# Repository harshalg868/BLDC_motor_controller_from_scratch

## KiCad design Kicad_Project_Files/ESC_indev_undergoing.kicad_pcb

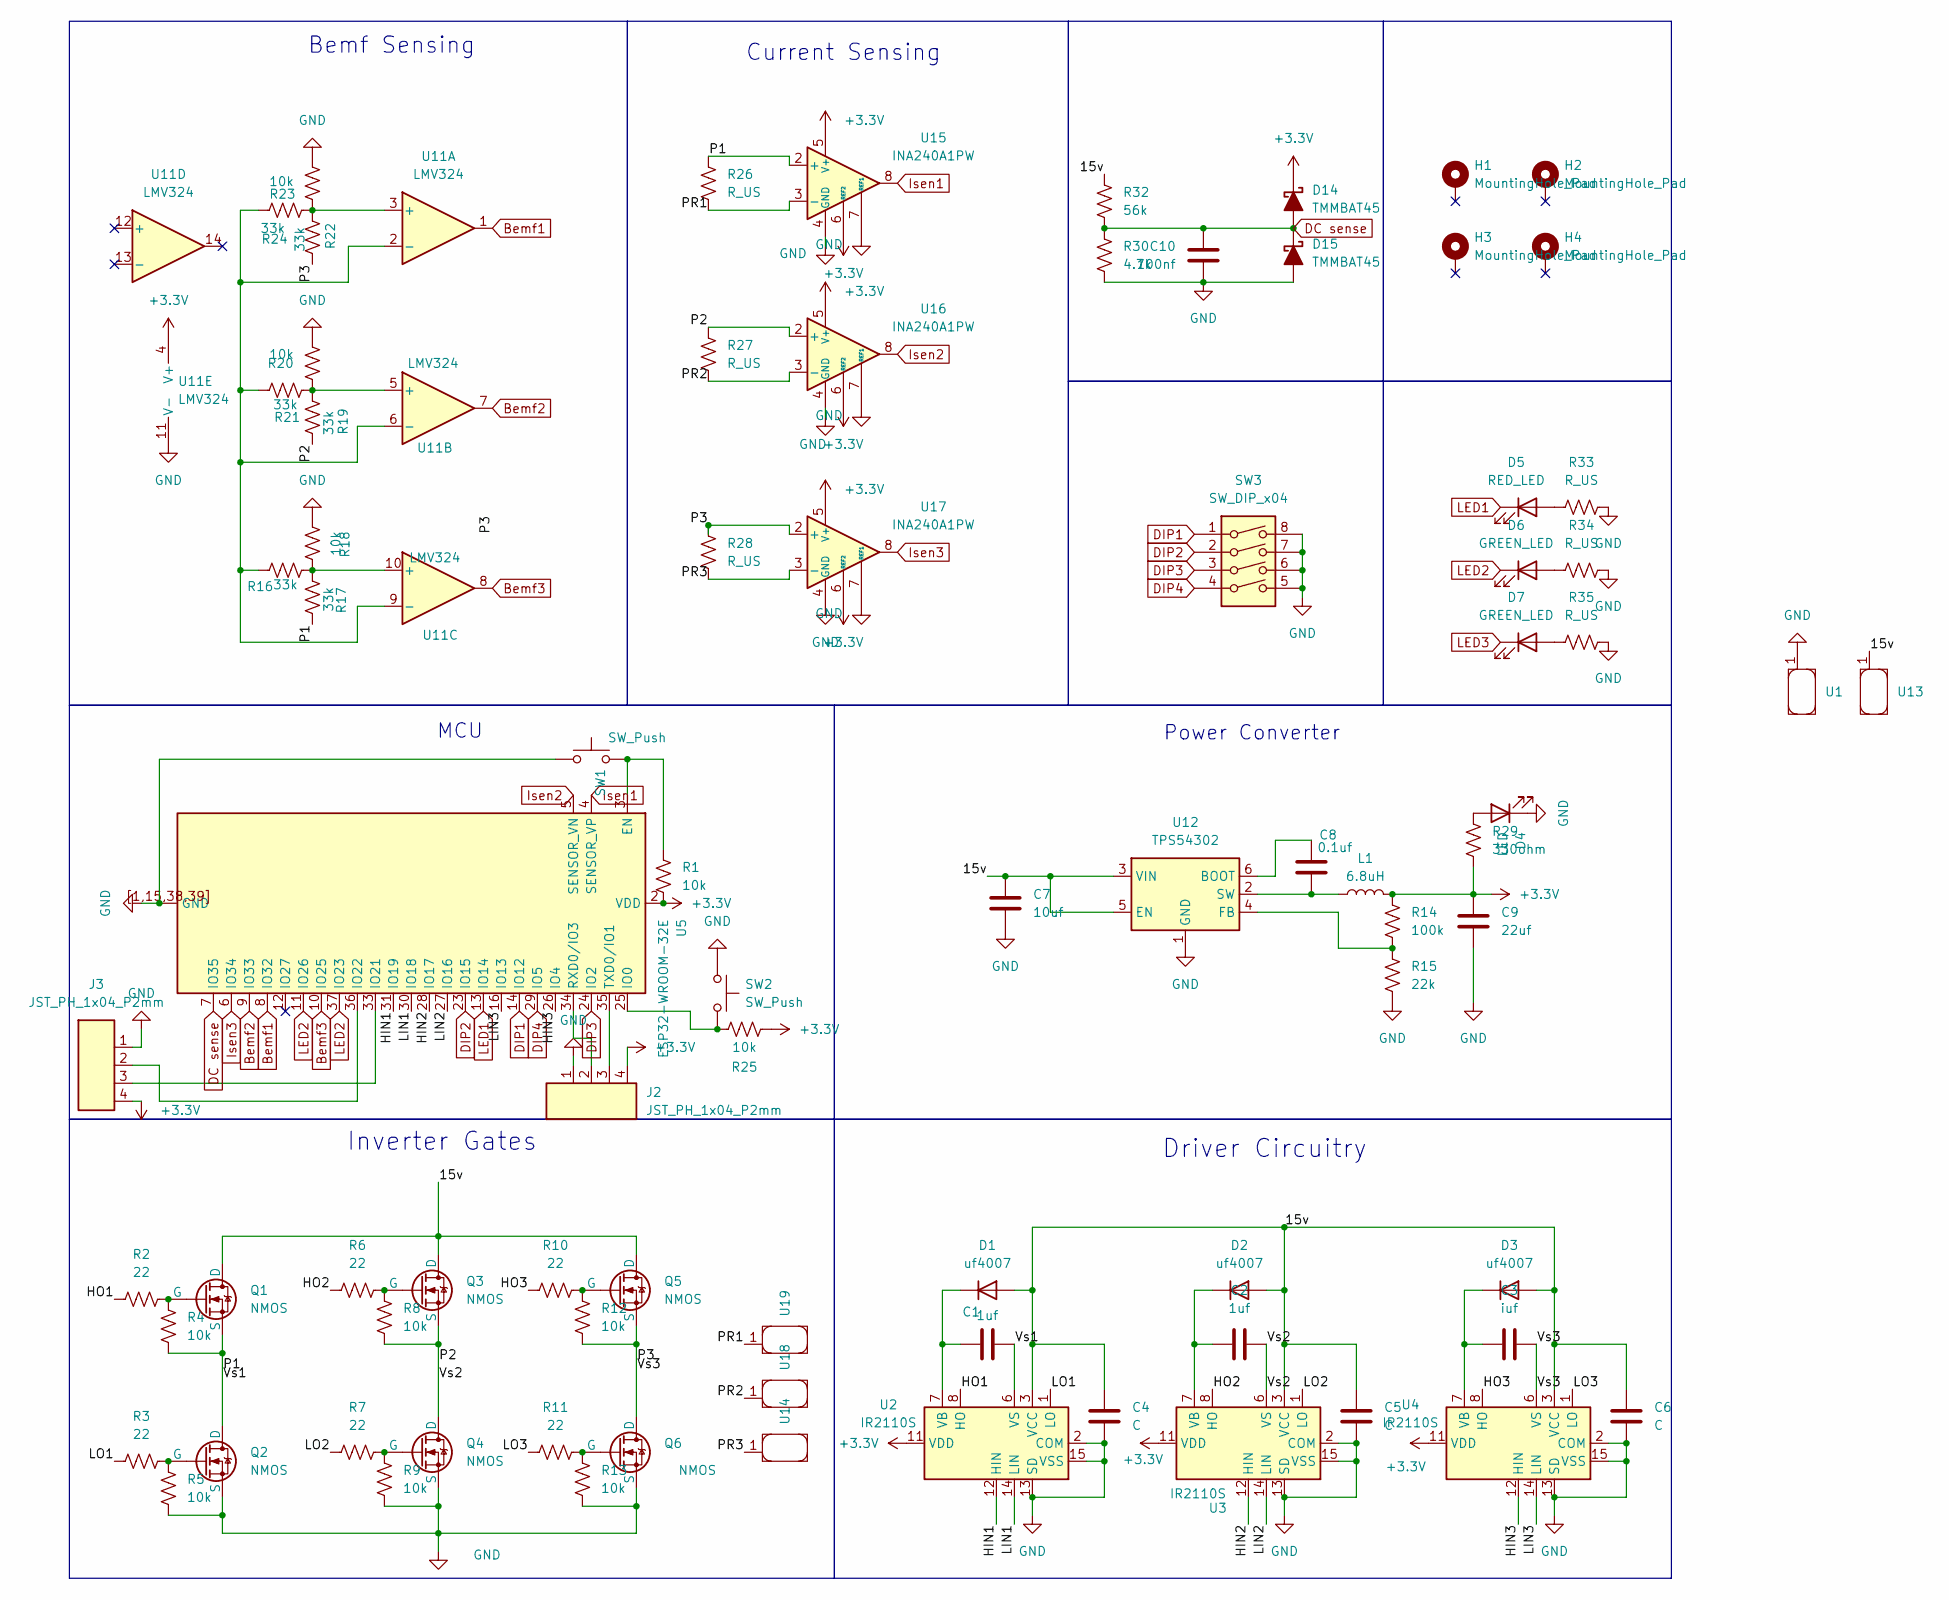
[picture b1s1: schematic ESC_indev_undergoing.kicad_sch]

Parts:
C1, C2: 1uf; C_1206_3216Metric
C3: iuf; C_1206_3216Metric
C4, C5, C6: C; C_0805_2012Metric
C7: 10uf; C_1206_3216Metric
C8: 0.1uf; C_0805_2012Metric
C9: 22uf; C_0805_2012Metric_Pad1.18x1.45mm_HandSolder
C10: 100nf; C_0805_2012Metric_Pad1.18x1.45mm_HandSolder
D1, D2, D3: uf4007; D_1206_3216Metric_Pad1.42x1.75mm_HandSolder
D4: LED; LED_0603_1608Metric_Pad1.05x0.95mm_HandSolder
D5: RED_LED; LED_1206_3216Metric
D6, D7: GREEN_LED; LED_1206_3216Metric
D14, D15: TMMBAT45; D_MiniMELF
H1, H2, H3, H4: MountingHole_Pad; MountingHole_3.2mm_M3_DIN965_Pad
J2, J3: JST_PH_1x04_P2mm; Header_JST_PH_1x04_P2mm_Vertical_SMD
L1: 6.8uH; L_6.3x6.3_H3
Q1, Q2, Q3, Q4, Q5, Q6: NMOS; TO-263-2
R1, R4, R5, R8, R9, R12, R13, R18, R20, R23, R25: 10k; R_0603_1608Metric_Pad1.05x0.95mm_HandSolder
R2, R3, R6, R7, R10, R11: 22; R_0603_1608Metric_Pad1.05x0.95mm_HandSolder
R14: 100k; R_0603_1608Metric_Pad1.05x0.95mm_HandSolder
R15: 22k; R_0603_1608Metric_Pad1.05x0.95mm_HandSolder
R16, R17, R19, R21, R22, R24: 33k; R_0603_1608Metric_Pad1.05x0.95mm_HandSolder
R26, R27, R28: R_US; R_2512_6332Metric_Pad1.40x3.35mm_HandSolder
R29: 330ohm; R_0805_2012Metric
R30: 4.7k; R_0805_2012Metric
R32: 56k; R_0805_2012Metric
R33, R34, R35: R_US; R_0603_1608Metric_Pad1.05x0.95mm_HandSolder
SW1, SW2: SW_Push; SW_Push_1P1T_NO_CK_KMR2
SW3: SW_DIP_x04; SW_DIP_SPSTx04_Slide_6.7x11.72mm_W8.61mm_P2.54mm_LowProfile
U1, U13, U14, U18, U19: Untitled
U2, U3, U4: IR2110S; SOIC-16W_7.5x10.3mm_P1.27mm
U5: ESP32-WROOM-32E
U11: LMV324; SOIC-14_3.9x8.7mm_P1.27mm
U12: TPS54302; SOT-23-6
U15, U16, U17: INA240A1PW; TSSOP-8_4.4x3mm_P0.65mm

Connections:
+3.3V: C9.1, D14.1 (K), J2.4, J3.4, L1.2, R1.2, R14.1, R25.2, R29.2, U2.11 (VDD), U3.11 (VDD), U4.11 (VDD), U5.2 (VDD), U11.4 (V+), U15.5 (V+), U15.6 (REF2), U16.5 (V+), U16.6 (REF2), U17.5 (V+), U17.6 (REF2)
/15v: C4.1, C5.1, C6.1, C7.1, D1.2 (A), D2.2 (A), D3.2 (A), Q1.1 (D), Q3.1 (D), Q5.1 (D), R32.1, U2.3 (VCC), U3.3 (VCC), U4.3 (VCC), U12.3 (VIN), U12.5 (EN), U13.1; also elsewhere on the board
/HIN1: U2.12 (HIN), U5.31 (IO19)
/HIN2: U3.12 (HIN), U5.28 (IO17)
/HIN3: U4.12 (HIN), U5.26 (IO4)
/HO1: R2.1, U2.8 (HO)
/HO2: R6.1, U3.8 (HO)
/HO3: R10.1, U4.8 (HO)
/LIN1: U2.14 (LIN), U5.30 (IO18)
/LIN2: U3.14 (LIN), U5.27 (IO16)
/LIN3: U4.14 (LIN), U5.16 (IO13)
/LO1: R3.1, U2.1 (LO)
/LO2: R7.1, U3.1 (LO)
/LO3: R11.1, U4.1 (LO)
/P1: C1.2, Q1.3 (S), Q2.1 (D), R4.1, R17.2, R26.1, U2.6 (VS), U15.2 (+)
/P2: C2.2, Q3.3 (S), Q4.1 (D), R8.1, R19.2, R27.1, U3.6 (VS), U16.2 (+)
/P3: C3.2, Q5.3 (S), Q6.1 (D), R12.1, R22.2, R28.1, U4.6 (VS), U17.2 (+)
/PR1: R26.2, U15.3 (-), U19.1; also elsewhere on the board
/PR2: R27.2, U16.3 (-), U18.1; also elsewhere on the board
/PR3: R28.2, U14.1, U17.3 (-); also elsewhere on the board
Bemf1: U5.8 (IO32), U11.1
Bemf2: U5.9 (IO33), U11.7
Bemf3: U5.10 (IO25), U11.8
DC sense: C10.1, D14.2 (A), D15.1 (K), R30.1, R32.2, U5.7 (IO35)
DIP1: SW3.1, U5.14 (IO12)
DIP2: SW3.2, U5.23 (IO15)
DIP3: SW3.3, U5.24 (IO2)
DIP4: SW3.4, U5.29 (IO5)
GND: C4.2, C5.2, C6.2, C7.2, C9.2, C10.2, D4.1 (K), D15.2 (A), J2.1, J3.1, Q2.3 (S), Q4.3 (S), Q6.3 (S), R5.1, R9.1, R13.1, R15.2, R18.1, R20.1, R23.1, R30.2, R33.2, R34.2, R35.2, SW1.1, SW2.1, SW3.5, SW3.6, SW3.7, SW3.8, U1.1, U2.2 (COM), U2.13 (SD), U2.15 (VSS), U3.2 (COM), U3.13 (SD), U3.15 (VSS), U4.2 (COM), U4.13 (SD), U4.15 (VSS), U5.1 (GND), U5.15 (GND), U5.38 (GND), U5.39 (GND), U5.[1,15,38,39] (GND), U11.11 (V-), U12.1 (GND), U15.1 (GND), U15.4 (GND), U15.7 (REF1), U16.1 (GND), U16.4 (GND), U16.7 (REF1), U17.1 (GND), U17.4 (GND), U17.7 (REF1); also elsewhere on the board
Isen1: U5.4 (SENSOR_VP), U15.8
Isen2: U5.5 (SENSOR_VN), U16.8
Isen3: U5.6 (IO34), U17.8
LED1: D5.1 (K), U5.13 (IO14)
LED2: D6.1 (K), U5.11 (IO26), U5.37 (IO23)
LED3: D7.1 (K)
unnamed: C1.1, D1.1 (K), U2.7 (VB)
unnamed: C2.1, D2.1 (K), U3.7 (VB)
unnamed: C3.1, D3.1 (K), U4.7 (VB)
unnamed: D4.2 (A), R29.1
unnamed: D5.2 (A), R33.1
unnamed: D6.2 (A), R34.1
unnamed: D7.2 (A), R35.1
unnamed: Q1.2 (G), R2.2, R4.2
unnamed: Q2.2 (G), R3.2, R5.2
unnamed: Q3.2 (G), R6.2, R8.2
unnamed: Q4.2 (G), R7.2, R9.2
unnamed: Q5.2 (G), R10.2, R12.2
unnamed: Q6.2 (G), R11.2, R13.2
unnamed: R1.1, SW1.2, U5.3 (EN)
unnamed: R25.1, SW2.2, U5.25 (IO0)
unnamed: J3.3, U5.33 (IO21)
unnamed: J3.2, U5.36 (IO22)
unnamed: J2.2, U5.34 (RXD0/IO3)
unnamed: J2.3, U5.35 (TXD0/IO1)
unnamed: R22.1, R23.2, R24.1, U11.3 (+)
unnamed: R16.2, R21.2, R24.2, U11.2 (-), U11.6 (-), U11.9 (-)
unnamed: R19.1, R20.2, R21.1, U11.5 (+)
unnamed: R16.1, R17.1, R18.2, U11.10 (+)
unnamed: C8.1, U12.6 (BOOT)
unnamed: R14.2, R15.1, U12.4 (FB)
unnamed: C8.2, L1.1, U12.2 (SW)

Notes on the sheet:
Power Converter
Inverter Gates
Driver Circuitry
MCU
Current Sensing
Bemf Sensing

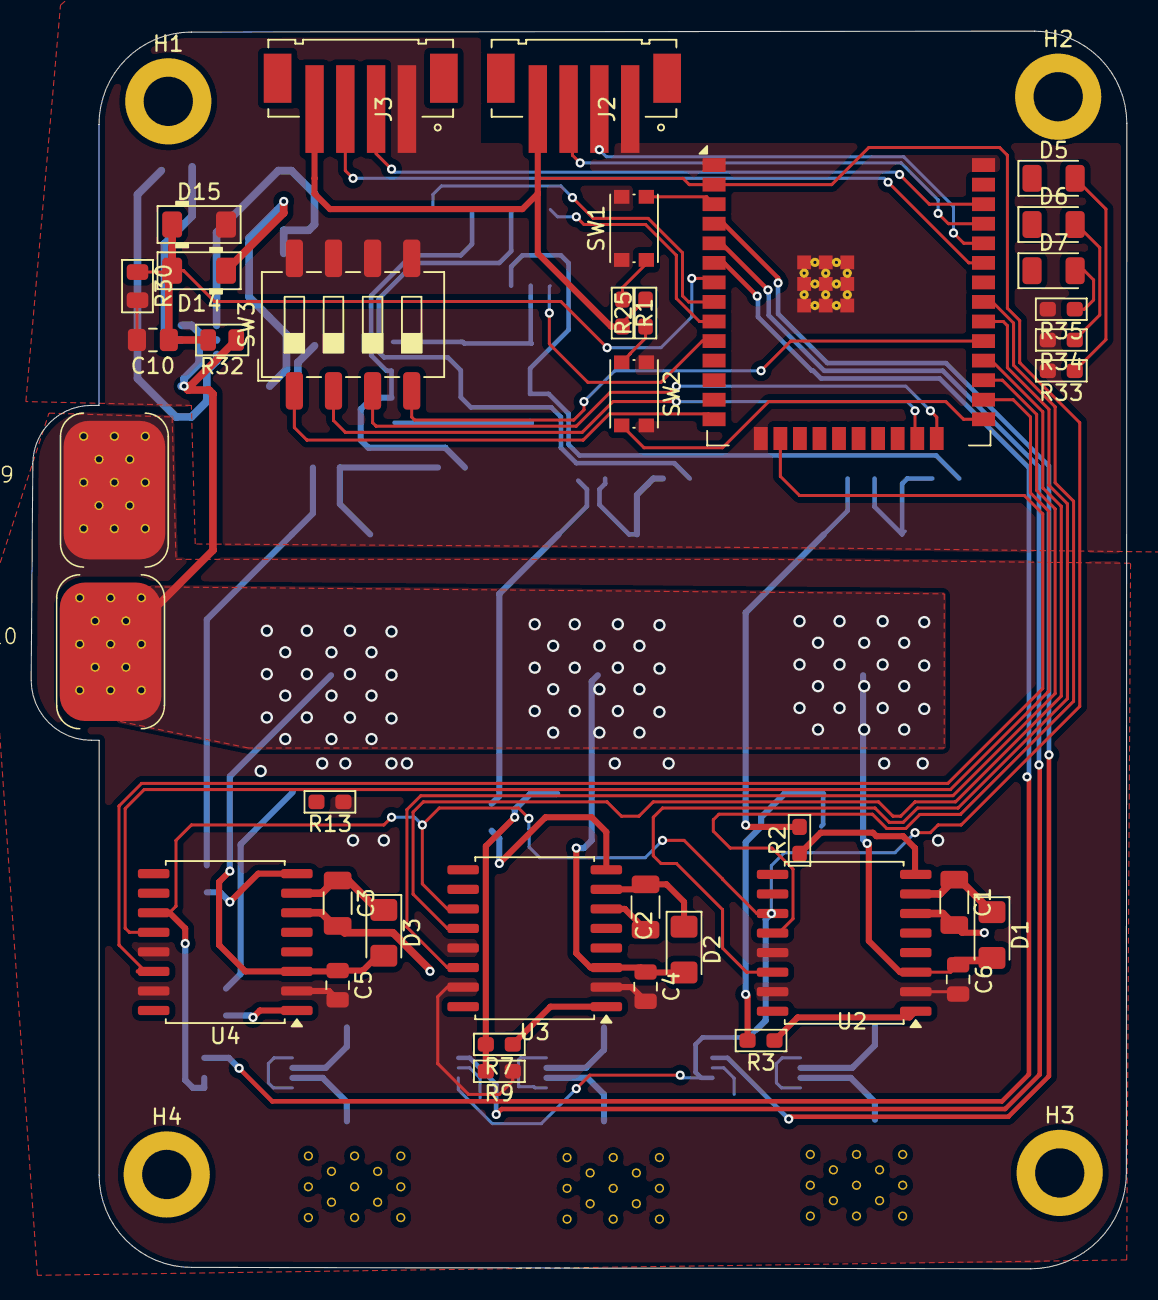
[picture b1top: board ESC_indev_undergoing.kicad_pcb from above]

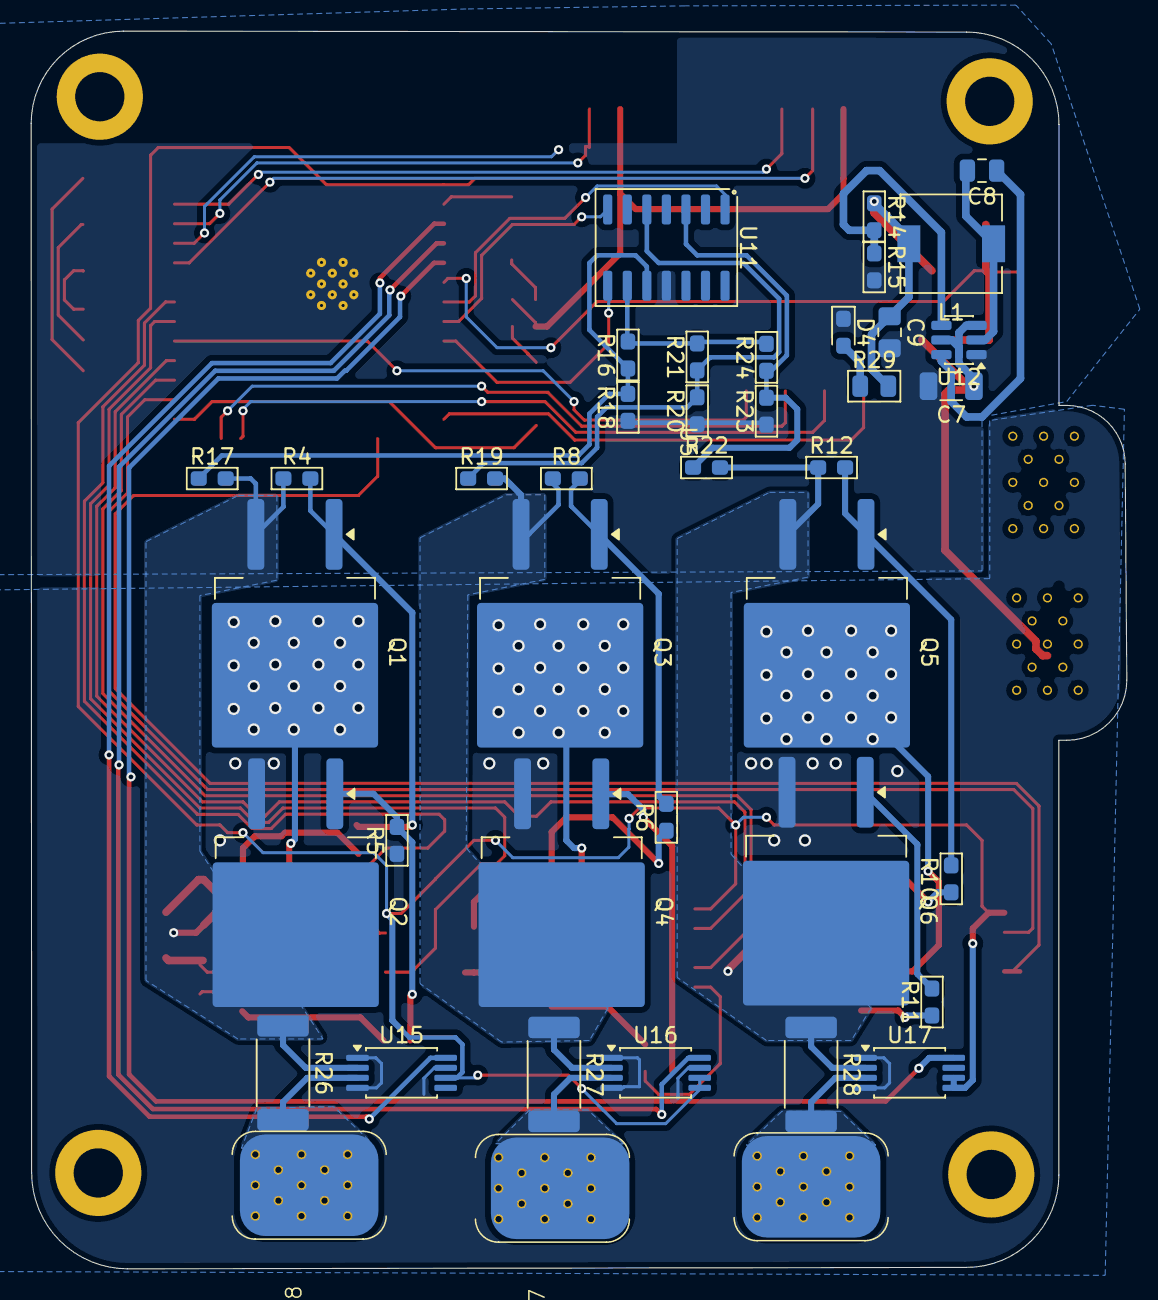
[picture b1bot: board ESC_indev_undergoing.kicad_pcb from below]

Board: 2 copper layers, 71.2 x 80.4 mm, 83 parts (41 on the bottom side), 60 nets.

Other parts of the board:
U6, U7, U8, U9, U10: Untitled

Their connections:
/15v: U10.1; also elsewhere on the board
/PR1: U8.2; also elsewhere on the board
/PR2: U7.2; also elsewhere on the board
/PR3: U6.2; also elsewhere on the board
GND: U9.1; also elsewhere on the board
